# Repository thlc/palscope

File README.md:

PalScope -- PAL to X-Y-Z Oscilloscope Raster
============================================

About
-----

PalScope is a KiCad version of the very nice schematic made by
[W2AEW](https://www.qsl.net/w2aew/), which converts a PAL signal into 
a 3-channel X-Y-Z raster that oscilloscopes can use to display a raster image.

Components
----------

The board is based around an LM1881 IC that extracts vertical and horizontal
sync pulses from the PAL signal. Those pulses are used to drive capacitors
that produce a 0-9V signal for the X and Y channels.

The Z channel is used to dim parts of the screen using an inverting opamp.
While W2AEW used an AD8032, I had to use an AD844 because I couldn't find
the 8032. This opamp isn't the best, especially since it's current-based.
If you can get hold of a 8032, go this way!

Pictures
--------

Schematic:

3-D rendering of the board:

An early working version of the PCB:

My Apple //e running Ultima IV:

Acknolwedgements
----------------

Thanks to Alan Wolke / W2AEW for publishing this design!
Make sure to check out his YouTube channel at https://www.youtube.com/@w2aew

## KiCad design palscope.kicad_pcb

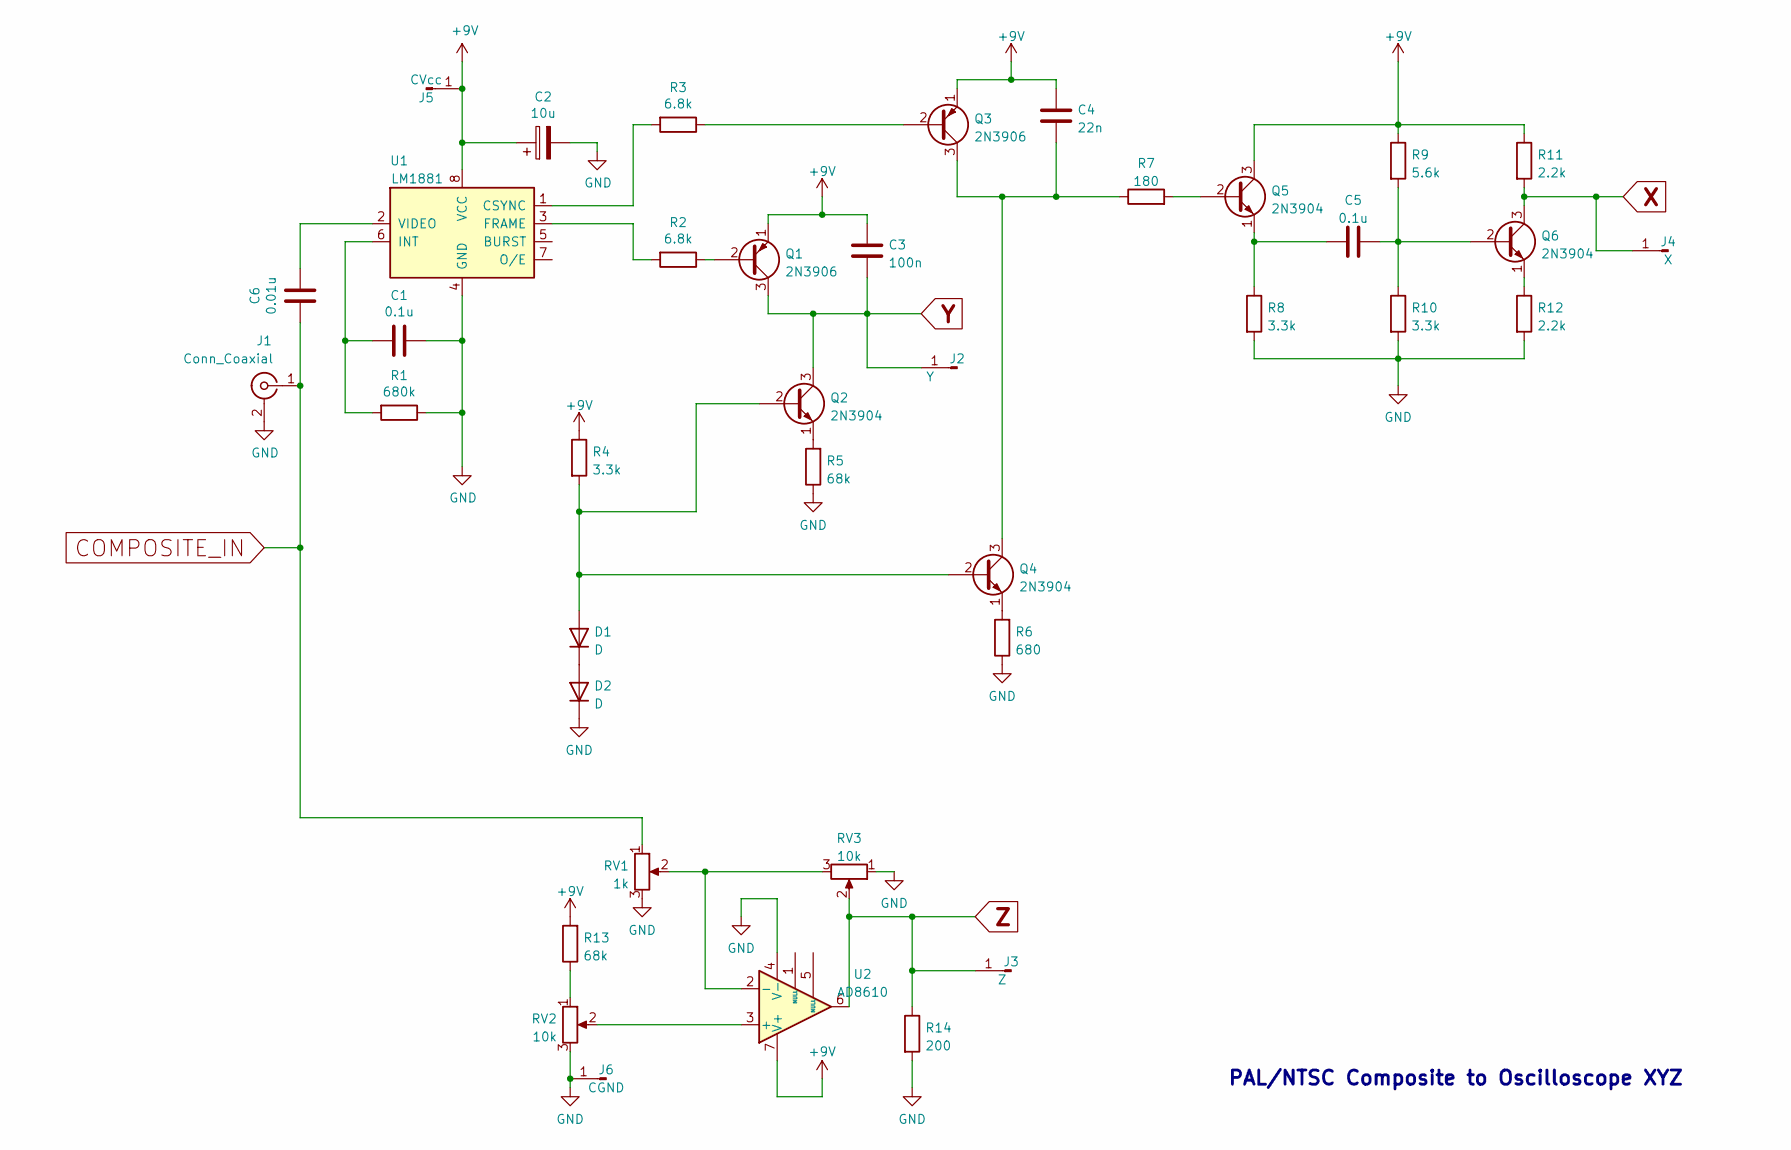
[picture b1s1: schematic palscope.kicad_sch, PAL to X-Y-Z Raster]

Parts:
C1, C5: 0.1u; C_Disc_D3.0mm_W1.6mm_P2.50mm
C2: 10u; CP_Radial_D5.0mm_P2.50mm
C3: 100n; C_Disc_D3.0mm_W1.6mm_P2.50mm
C4: 22n; C_Disc_D3.0mm_W1.6mm_P2.50mm
C6: 0.01u; C_Disc_D3.0mm_W1.6mm_P2.50mm
D1, D2: D; D_A-405_P2.54mm_Vertical_AnodeUp
J1: Conn_Coaxial; CUI_RCJ-013
J2: Y; PinHeader_1x01_P2.54mm_Vertical
J3: Z; PinHeader_1x01_P2.54mm_Vertical
J4: X; PinHeader_1x01_P2.54mm_Vertical
J5: CVcc; PinHeader_1x01_P2.54mm_Vertical
J6: CGND; PinHeader_1x01_P2.54mm_Vertical
Q1, Q3: 2N3906; TO-92_Inline_Wide
Q2, Q4, Q5, Q6: 2N3904; TO-92_Inline_Wide
R1: 680k; R_Axial_DIN0204_L3.6mm_D1.6mm_P2.54mm_Vertical
R2, R3: 6.8k; R_Axial_DIN0204_L3.6mm_D1.6mm_P2.54mm_Vertical
R4, R8, R10: 3.3k; R_Axial_DIN0204_L3.6mm_D1.6mm_P2.54mm_Vertical
R5, R13: 68k; R_Axial_DIN0204_L3.6mm_D1.6mm_P2.54mm_Vertical
R6: 680; R_Axial_DIN0204_L3.6mm_D1.6mm_P2.54mm_Vertical
R7: 180; R_Axial_DIN0204_L3.6mm_D1.6mm_P2.54mm_Vertical
R9: 5.6k; R_Axial_DIN0204_L3.6mm_D1.6mm_P2.54mm_Vertical
R11, R12: 2.2k; R_Axial_DIN0204_L3.6mm_D1.6mm_P2.54mm_Vertical
R14: 200; R_Axial_DIN0204_L3.6mm_D1.6mm_P2.54mm_Vertical
RV1: 1k; Potentiometer_Bourns_3386F_Vertical_copy
RV2, RV3: 10k; Potentiometer_Bourns_3386F_Vertical_copy
U1: LM1881; DIP-8_W7.62mm
U2: AD8610; DIP-8_W7.62mm_Socket

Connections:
+9V: C2.1, C3.1, C4.1, J5.1, Q1.1 (E), Q3.1 (E), Q5.3 (C), R4.1, R9.1, R11.1, R13.2, U1.8 (VCC), U2.7 (V+)
COMPOSITE_IN: C6.2, J1.1 (In), RV1.1
GND: C1.1, C2.2, D2.1 (K), J1.2 (Ext), J6.1, R1.1, R5.1, R6.1, R8.2, R10.2, R12.2, R14.2, RV1.3, RV2.3, RV3.1, U1.4 (GND), U2.4 (V-)
unnamed: C1.2, R1.2, U1.6 (INT)
unnamed: C4.2, Q3.3 (C), Q4.3 (C), R7.1
unnamed: C5.1, Q5.1 (E), R8.1
unnamed: C5.2, Q6.2 (B), R9.2, R10.1
unnamed: C6.1, U1.2 (VIDEO)
unnamed: D1.1 (K), D2.2 (A)
unnamed: D1.2 (A), Q2.2 (B), Q4.2 (B), R4.2
unnamed: Q1.2 (B), R2.1
unnamed: Q2.1 (E), R5.2
unnamed: Q3.2 (B), R3.1
unnamed: Q4.1 (E), R6.2
unnamed: Q5.2 (B), R7.2
unnamed: Q6.1 (E), R12.1
unnamed: R2.2, U1.3 (FRAME)
unnamed: R3.2, U1.1 (CSYNC)
unnamed: R13.1, RV2.1
unnamed: RV1.2, RV3.3, U2.2 (-)
unnamed: RV2.2, U2.3 (+)
X: J4.1, Q6.3 (C), R11.2
Y: C3.2, J2.1, Q1.3 (C), Q2.3 (C)
Z: J3.1, R14.1, RV3.2, U2.6

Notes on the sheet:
PAL/NTSC Composite to Oscilloscope XYZ

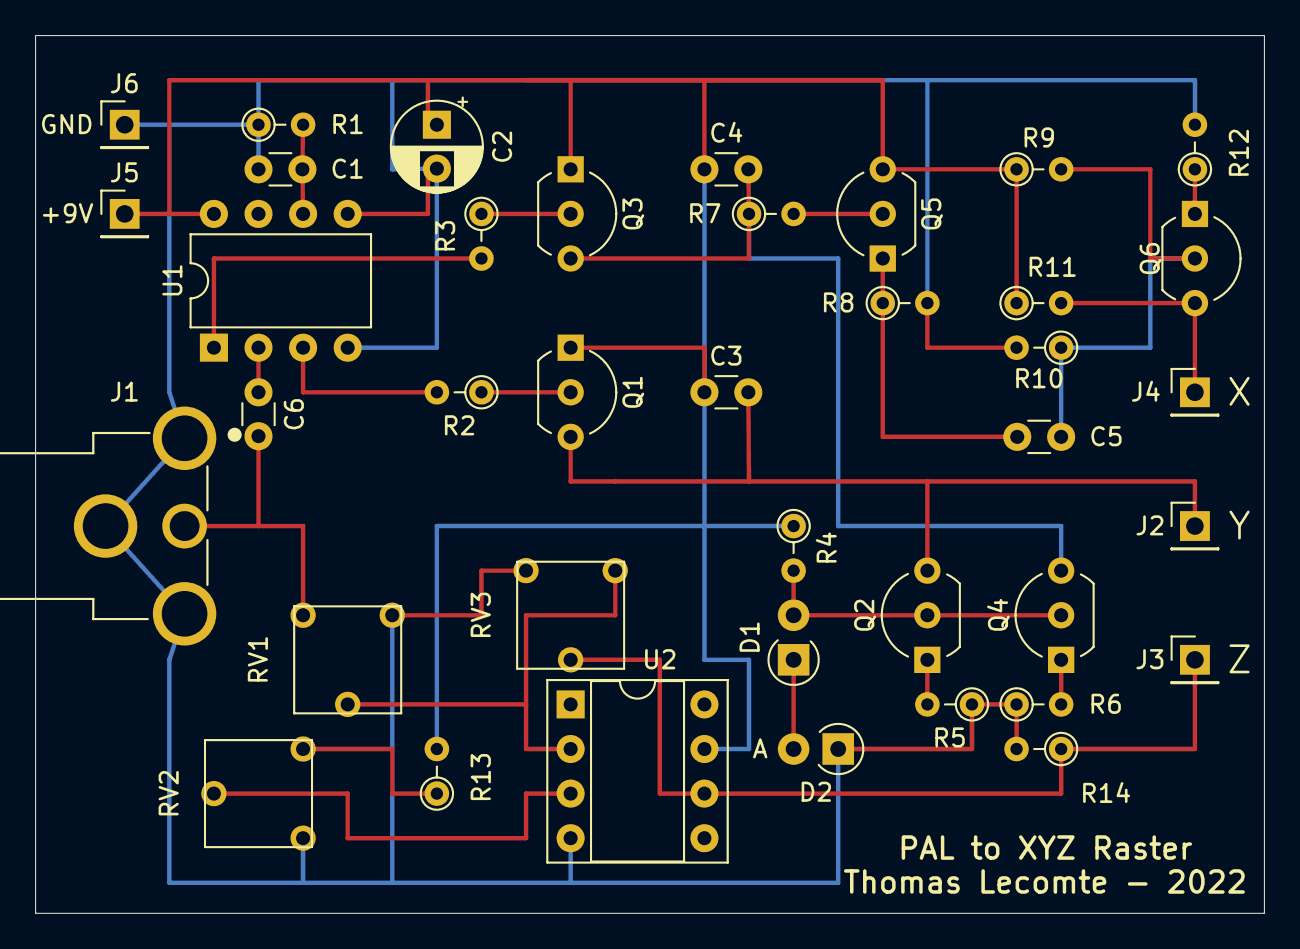
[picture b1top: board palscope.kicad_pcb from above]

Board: 2 copper layers, 70.0 x 50.0 mm, 39 parts (0 on the bottom side), 24 nets.

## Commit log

2022-11-13 PALscope KiCad Project
2022-12-04 reworked PCB, removed useless connections, fixed bad C6 capacity
2022-12-04 Added readme, images, removed useless backup files
2022-12-04 fixed paths
2022-12-04 Updated images
2022-12-04 fix in README
